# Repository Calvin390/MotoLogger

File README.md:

# Motologger

**Motologger** is a modular motorcycle data logger built around an ESP32-S3.  
The goal of the project is to record useful riding and vehicle dynamics data from a motorcycle that does not have a factory ECU or CAN bus.
The system is designed to collect data from external sensor modules over CAN and log it to a microSD card for later analysis.

> Current target platform: 2001 Suzuki SV650  
> Current firmware target: ESP32-S3 using ESP-IDF in C with FreeRTOS task/queue architecture

---

## Project Goals

Motologger is intended to be a compact, low-cost motorcycle telemetry system capable of logging:
- IMU data such as acceleration, gyro, and estimated lean angle
- GPS position and speed
- CAN messages from external daughterboards
- Timestamped CSV data to a microSD card
- Future expansion for additional sensors such as throttle position, brake pressure, wheel speed, and steering angle

The long-term goal is to build a modular logging and display system that can support both post-ride analysis and a future visor-mounted HUD.

---

## Current Status

**Status: PCB Bring-up and Firmware Flashing 

The prototype board has been assembled and is ready to be flashed using backup UART via ESP32 pins instead of USB-C due to anchoring issues with the receptacle. The ESP32 has been confirmed alive by both oscilloscope readings and reading TX data through TeraTerm coming from the ESP32.

Current focus:
Flashing firmware via UART to the ESP32 and confirming proper idle CAN traffic through an oscilloscope.

Hardware is in its first prototype revision and may change in future spins based on bring-up results.
---

## System Overview

The Motologger system is split into a main controller board and external sensor modules.

```text
        +--------------------+
        |    GPS Module      |
        |   u-blox M10       |
        +----------+---------+
                   |
                   | CAN
                   |
 +-----------------v-----------------+
|          Motologger Mainboard      |
|                                    |
| ESP32-S3-WROOM                     |
|  Power Stage (fuse/TVS/Schottky,   |
|    12V→5V→3.3V regulation)         |
|  microSD Card                      |
|  CAN Transceiver                   |
|  USB-C Debug/Programming           |
|  12V Motorcycle Power Input        |
 +-----------------^-----------------+
                   |
                   | CAN
                   |
        +----------+---------+
        |     IMU Module     |
        |   ICM-20948        |
        +--------------------+

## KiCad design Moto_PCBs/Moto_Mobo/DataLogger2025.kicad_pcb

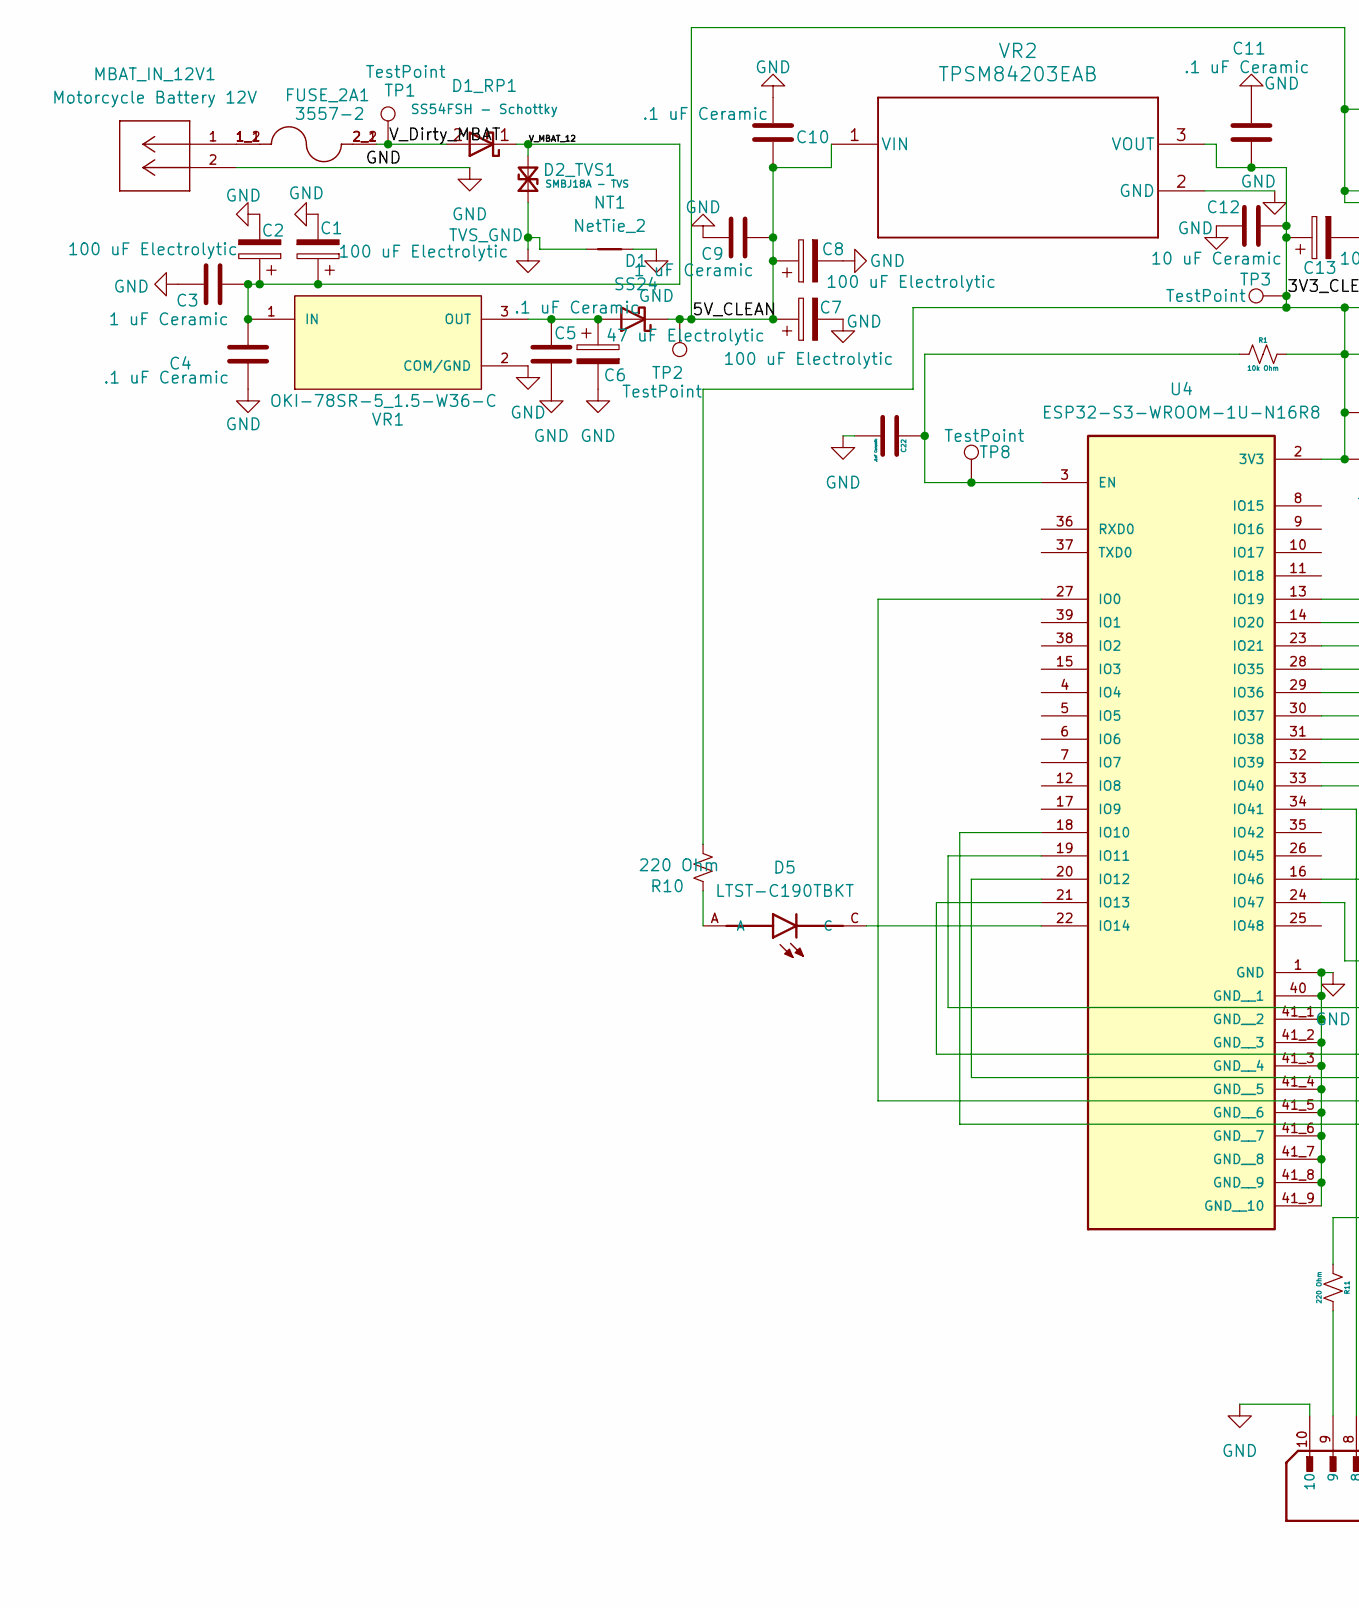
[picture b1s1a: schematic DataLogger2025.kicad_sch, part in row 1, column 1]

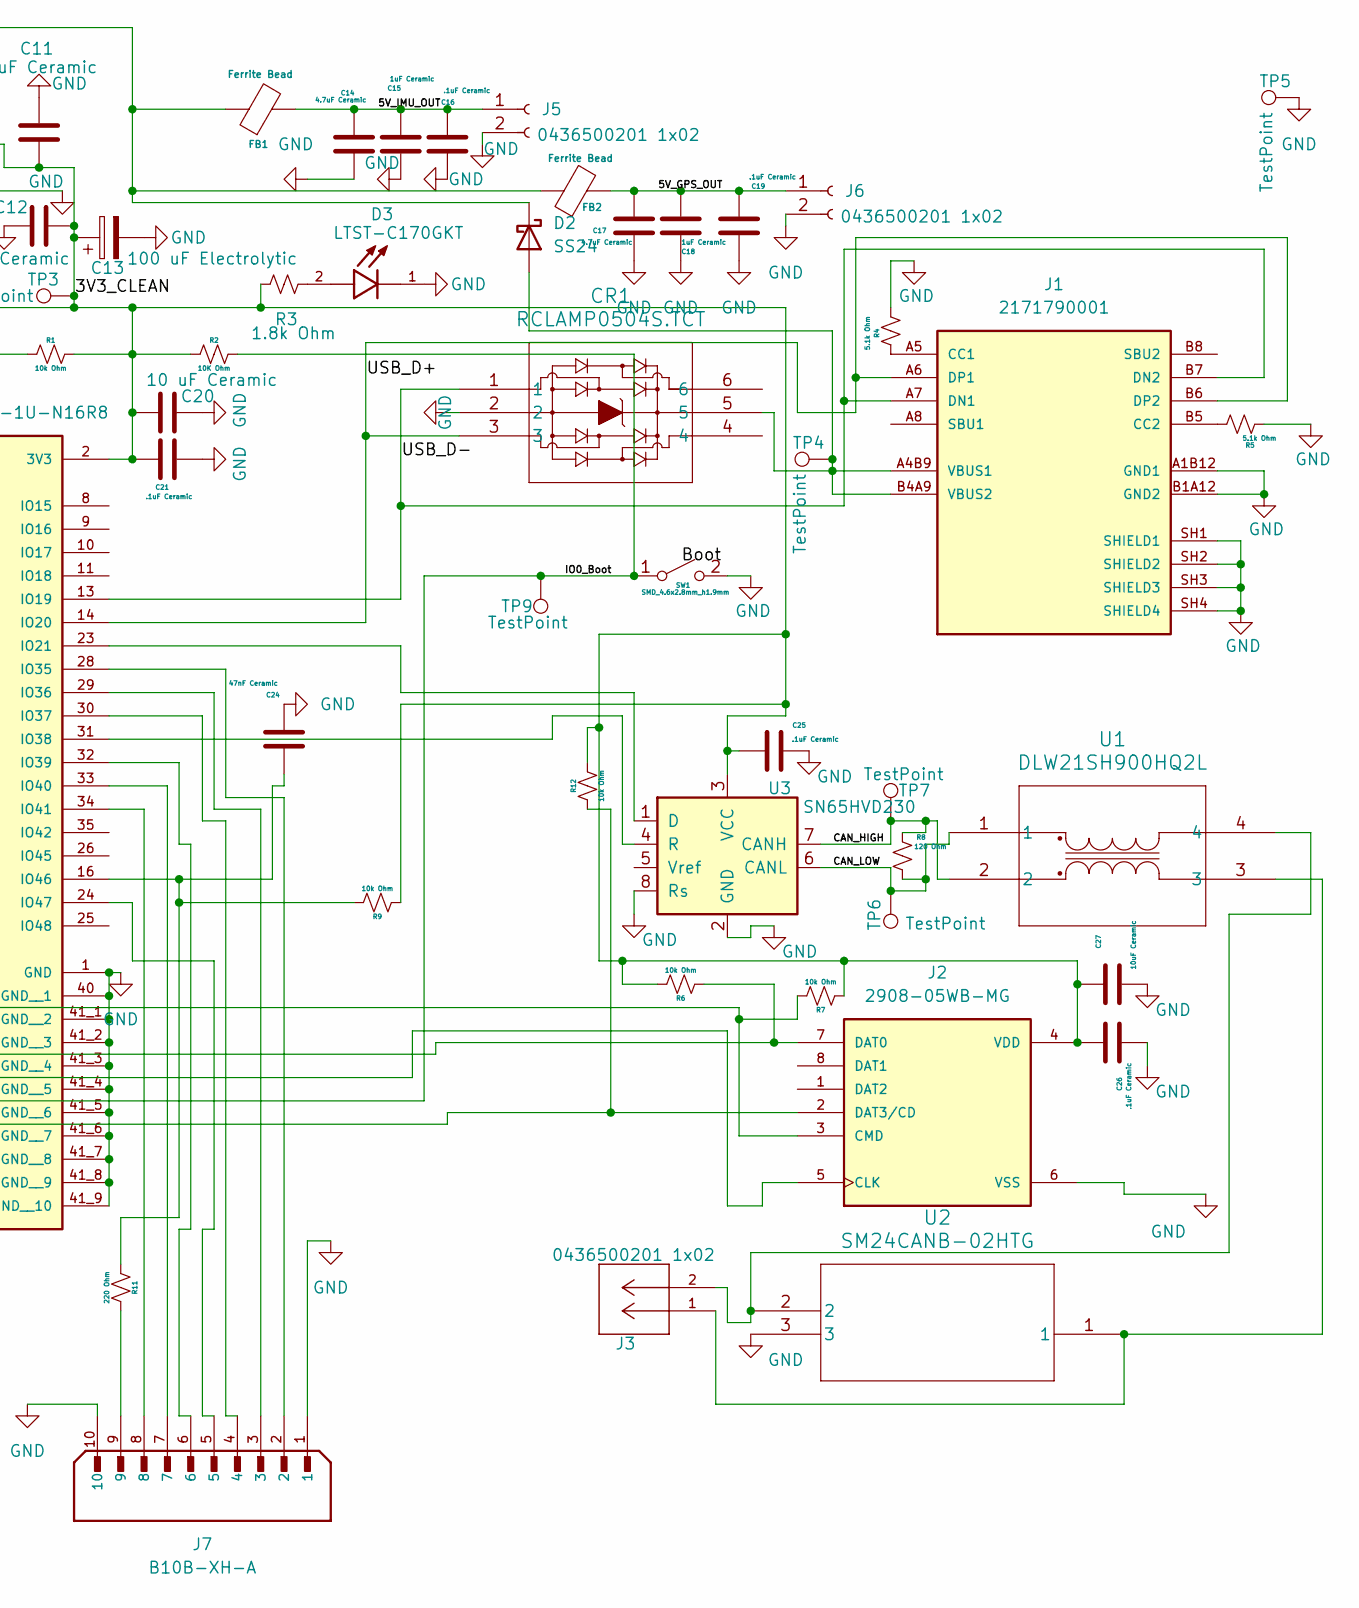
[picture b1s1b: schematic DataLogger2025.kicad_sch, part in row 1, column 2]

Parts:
C1, C2, C7, C8, C13: 100 uF Electrolytic; CP_Radial_D8.0mm_P2.50mm
C3, C9: 1 uF Ceramic; C_1206_3216Metric_Pad1.33x1.80mm_HandSolder
C4, C5, C10, C11: .1 uF Ceramic; C_1206_3216Metric_Pad1.33x1.80mm_HandSolder
C6: 47 uF Electrolytic; CP_Radial_D6.3mm_P2.50mm
C12, C20: 10 uF Ceramic; C_1206_3216Metric_Pad1.33x1.80mm_HandSolder
C14, C17: 4.7uF Ceramic; C_1206_3216Metric_Pad1.33x1.80mm_HandSolder
C15, C18: 1uF Ceramic; C_1206_3216Metric_Pad1.33x1.80mm_HandSolder
C16, C19, C21, C22, C25, C26: .1uF Ceramic; C_1206_3216Metric_Pad1.33x1.80mm_HandSolder
C24: 47nF Ceramic; C_1206_3216Metric_Pad1.33x1.80mm_HandSolder
C27: 10uF Ceramic; C_1206_3216Metric_Pad1.33x1.80mm_HandSolder
CR1: RCLAMP0504S.TCT; SC70-6L_RCLAMP_1p75x3p1-0p95_SEM
D1, D2: SS24; SOD-123F_ONS
D1_RP1: SS54FSH - Schottky; D_SMB
D2_TVS1: SMBJ18A - TVS; D_SMB_Handsoldering
D3: LTST-C170GKT; LED_LTST-C170GKT; PARTREV I; DigiKey_Part_Number 160-1179-1-ND
D5: LTST-C190TBKT; LEDM1608X80; DigiKey_Part_Number 160-1646-1-ND
FB1, FB2: Ferrite Bead; L_1206_3216Metric_Pad1.42x1.75mm_HandSolder
FUSE_2A1: 3557-2; FUSE_3557-2; PARTREV D; DigiKey_Part_Number 36-3557-2-ND
J1: 2171790001; MOLEX_2171790001; PARTREV A1; DigiKey_Part_Number 900-2171790001CT-ND
J2: 2908-05WB-MG; 3M_2908-05WB-MG; DigiKey_Part_Number 3M5607CT-ND
J3: 0436500201 1x02; CONN_SD-43650-001_02_MOL; MANUFACTURER_PART_NUMBER 436500201
J5, J6: 0436500201 1x02; Molex_Micro-Fit_3.0_43650-0200_1x02_P3.00mm_Horizontal
J7: B10B-XH-A; JST_B10B-XH-A; PARTREV 7/4/21; DigiKey_Part_Number 455-B10B-XH-A-ND
MBAT_IN_12V1: Motorcycle Battery 12V; CONN_SD-43650-001_02_MOL; MANUFACTURER_PART_NUMBER 436500201
NT1: NetTie_2; NetTie-2_SMD_Pad0.5mm
R1, R6, R7, R9, R12: 10k Ohm; R_1206_3216Metric_Pad1.30x1.75mm_HandSolder
R2: 10K Ohm; R_1206_3216Metric_Pad1.30x1.75mm_HandSolder
R3: 1.8k Ohm; R_1206_3216Metric_Pad1.30x1.75mm_HandSolder
R4, R5: 5.1k Ohm; R_1206_3216Metric_Pad1.30x1.75mm_HandSolder
R8: 120 Ohm; R_Axial_DIN0204_L3.6mm_D1.6mm_P5.08mm_Horizontal
R10, R11: 220 Ohm; R_1206_3216Metric_Pad1.30x1.75mm_HandSolder
SW1: SMD_4.6x2.8mm_h1.9mm; Push_SMD_4.6x2.8mm_h1.9mm
TP1, TP2, TP3, TP4, TP5, TP6, TP7, TP9: TestPoint; TestPoint_Pad_1.5x1.5mm
TP8: TestPoint; TestPoint_Pad_1.0x1.0mm
U1: DLW21SH900HQ2L; DLW21SH_MUR
U2: SM24CANB-02HTG; SOT23-3_SM24CANB-02HTG_LTF
U3: SN65HVD230; SOIC-8_3.9x4.9mm_P1.27mm
U4: ESP32-S3-WROOM-1U-N16R8; XCVR_ESP32-S3-WROOM-1U-N16R8; PARTREV v1.1; DigiKey_Part_Number 1965-ESP32-S3-WROOM-1U-N16R8CT-ND
VR1: OKI-78SR-5_1.5-W36-C; CONV_OKI-78SR-5_1.5-W36-C; PARTREV N/A; DigiKey_Part_Number 811-2196-5-ND
VR2: TPSM84203EAB; EAB0003A

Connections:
/3V3_CLEAN: C11.2, C12.2, C13.1, C20.2, C21.1, C25.1, C26.1, C27.1, J2.4 (VDD), R1.1, R2.2, R3.1, R6.1, R7.2, R9.2, R10.1, R12.1, TP3.1 (1_1), U3.3 (VCC), U4.2 (3V3), VR2.3 (VOUT)
/5V_CLEAN: C7.1, C8.1, C9.2, C10.2, D1.1 (K), D2.1 (K), FB1.1, FB2.1, TP2.1 (1_1), VR2.1 (VIN)
/5V_GPS_OUT: C17.1, C18.1, C19.1, FB2.2, J6.1
/5V_IMU_OUT: C14.1, C15.1, C16.1, FB1.2, J5.1
/CAN_HIGH: R8.2, TP7.1 (1_1), U1.2, U3.7 (CANH)
/CAN_LOW: R8.1, TP6.1 (1_1), U1.1, U3.6 (CANL)
/IO0_Boot: R2.1, SW1.1 (A), TP9.1 (1_1), U4.27 (IO0)
/USB_D+: CR1.3, J1.A6 (DP1), J1.B6 (DP2), U4.14 (IO20)
/USB_D-: CR1.1, J1.A7 (DN1), J1.B7 (DN2), U4.13 (IO19)
/V_Dirty_MBAT: D1_RP1.2 (A), FUSE_2A1.2_1, FUSE_2A1.2_2, TP1.1 (1_1)
/V_MBAT_12: C1.1, C2.1, C3.2, C4.2, D1_RP1.1 (K), D2_TVS1.2 (A2), VR1.1 (IN)
GND: C1.2, C2.2, C3.1, C4.1, C5.1, C6.2, C7.2, C8.2, C9.1, C10.1, C11.1, C12.1, C13.2, C14.2, C15.2, C16.2, C17.2, C18.2, C19.2, C20.1, C21.2, C22.2, C24.1, C25.2, C26.2, C27.2, CR1.2, D3.1, J1.A1B12 (GND1), J1.B1A12 (GND2), J1.SH1 (SHIELD1), J1.SH2 (SHIELD2), J1.SH3 (SHIELD3), J1.SH4 (SHIELD4), J2.6 (VSS), J5.2, J6.2, J7.1, J7.10, MBAT_IN_12V1.2, NT1.2, R4.1, R5.1, SW1.2 (B), TP5.1 (1_1), U2.3, U3.2 (GND), U3.8 (Rs), U4.1 (GND), U4.40 (GND__1), U4.41_1 (GND__2), U4.41_2 (GND__3), U4.41_3 (GND__4), U4.41_4 (GND__5), U4.41_5 (GND__6), U4.41_6 (GND__7), U4.41_7 (GND__8), U4.41_8 (GND__9), U4.41_9 (GND__10), VR1.2 (COM/GND), VR2.2 (GND)
unnamed: C5.2, C6.1, D1.2 (A), VR1.3 (OUT)
unnamed: CR1.5, D2.2 (A), J1.A4B9 (VBUS1), J1.B4A9 (VBUS2), TP4.1 (1_1)
unnamed: D3.2, R3.2
unnamed: D5.A, R10.2
unnamed: FUSE_2A1.1_1, FUSE_2A1.1_2, MBAT_IN_12V1.1
unnamed: J1.A5 (CC1), R4.2
unnamed: J1.B5 (CC2), R5.2
unnamed: J2.5 (CLK), U4.20 (IO12)
unnamed: J2.3 (CMD), R7.1, U4.19 (IO11)
unnamed: J2.7 (DAT0), R6.2, U4.21 (IO13)
unnamed: J2.2 (DAT3/CD), R12.2, U4.18 (IO10)
unnamed: J3.1, U1.3, U2.1
unnamed: J3.2, U1.4, U2.2
unnamed: J7.9, R11.1
unnamed: U3.1 (D), U4.23 (IO21)
unnamed: U3.4 (R), U4.31 (IO38)
unnamed: C22.1, R1.2, TP8.1 (1_1), U4.3 (EN)
unnamed: D5.C, U4.22 (IO14)
unnamed: J7.2, U4.28 (IO35)
unnamed: J7.3, U4.29 (IO36)
unnamed: J7.4, U4.30 (IO37)
unnamed: J7.6, U4.32 (IO39)
unnamed: J7.7, U4.33 (IO40)
unnamed: J7.8, U4.34 (IO41)
unnamed: C24.2, R9.1, R11.2, U4.16 (IO46)
unnamed: J7.5, U4.24 (IO47)
TVS_GND: D2_TVS1.1 (A1), NT1.1

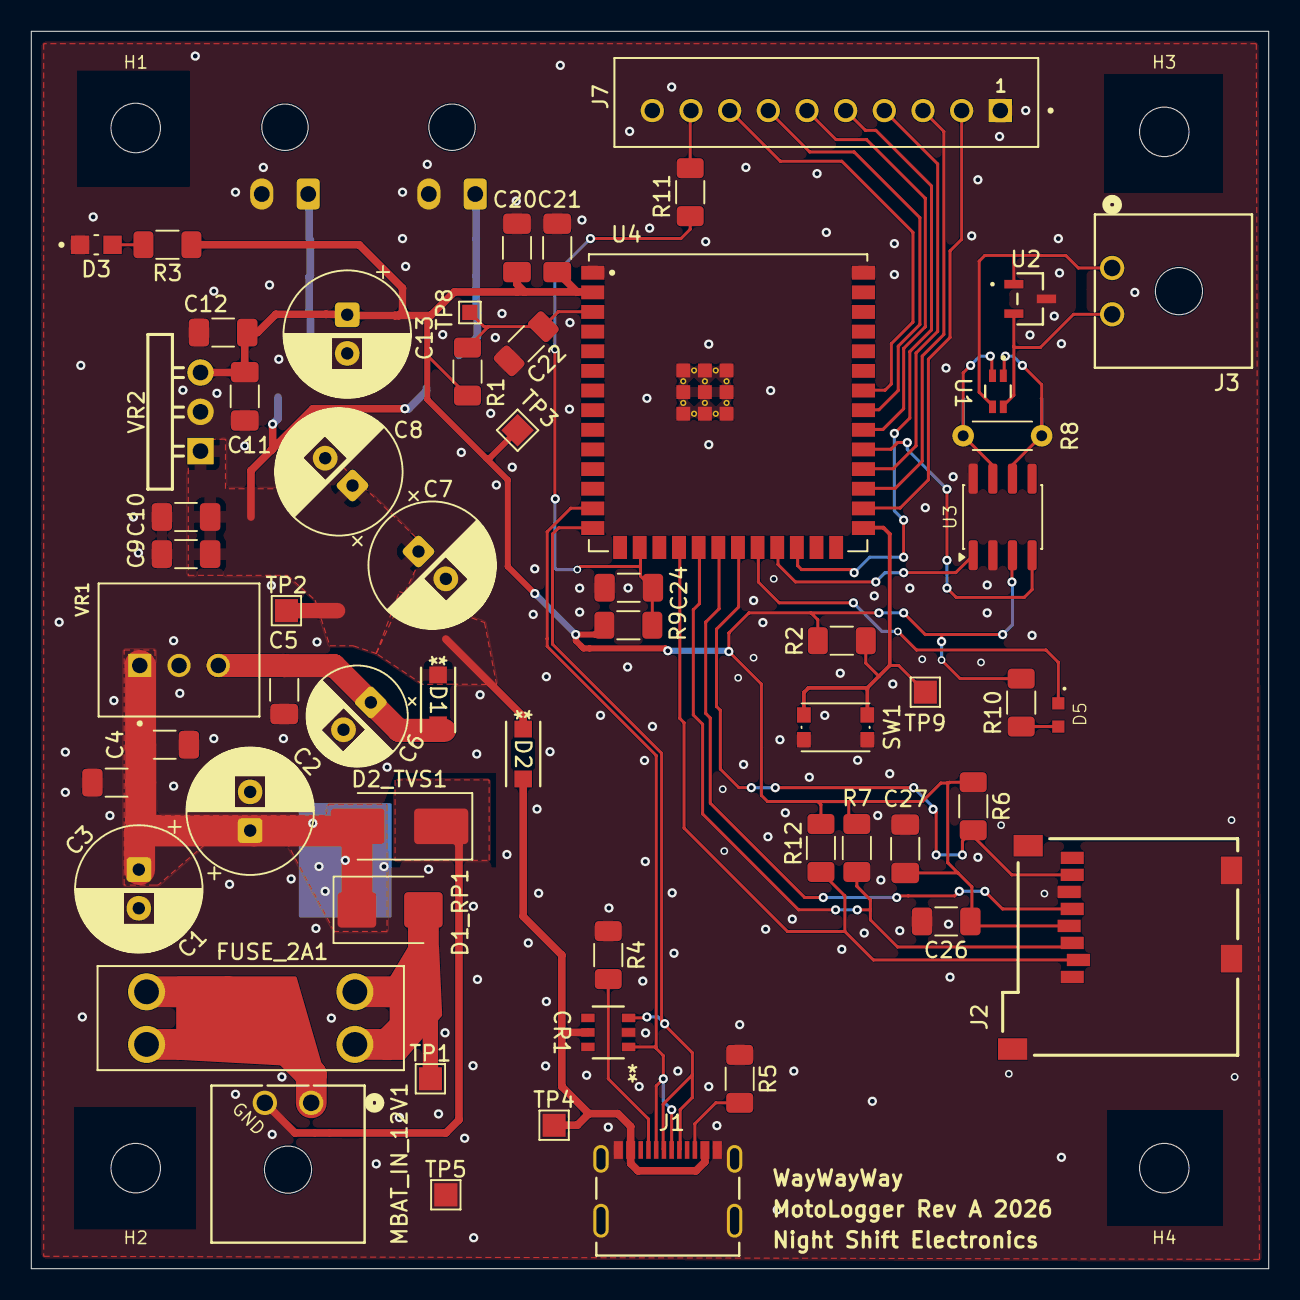
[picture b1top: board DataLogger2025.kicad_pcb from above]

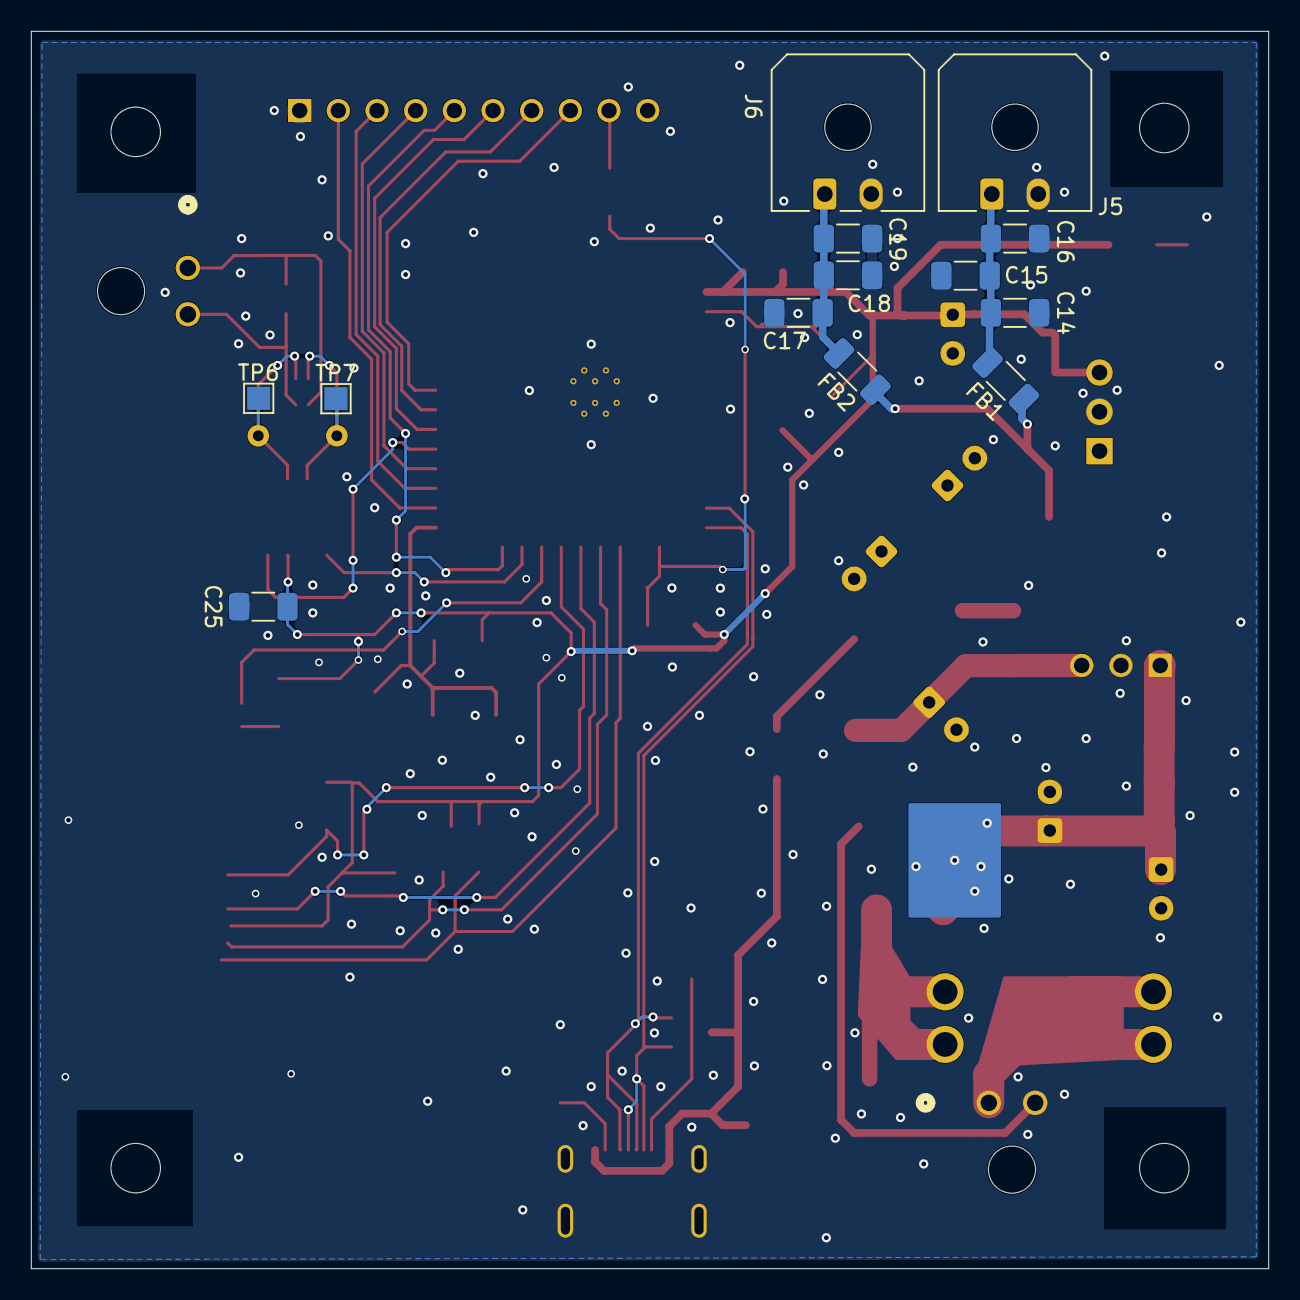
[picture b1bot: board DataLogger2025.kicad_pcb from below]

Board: 2 copper layers, 80.0 x 80.0 mm, 76 parts (13 on the bottom side), 39 nets.

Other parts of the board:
H1, H2, H3, H4: MountingHole; MountingHole_3.2mm_M3

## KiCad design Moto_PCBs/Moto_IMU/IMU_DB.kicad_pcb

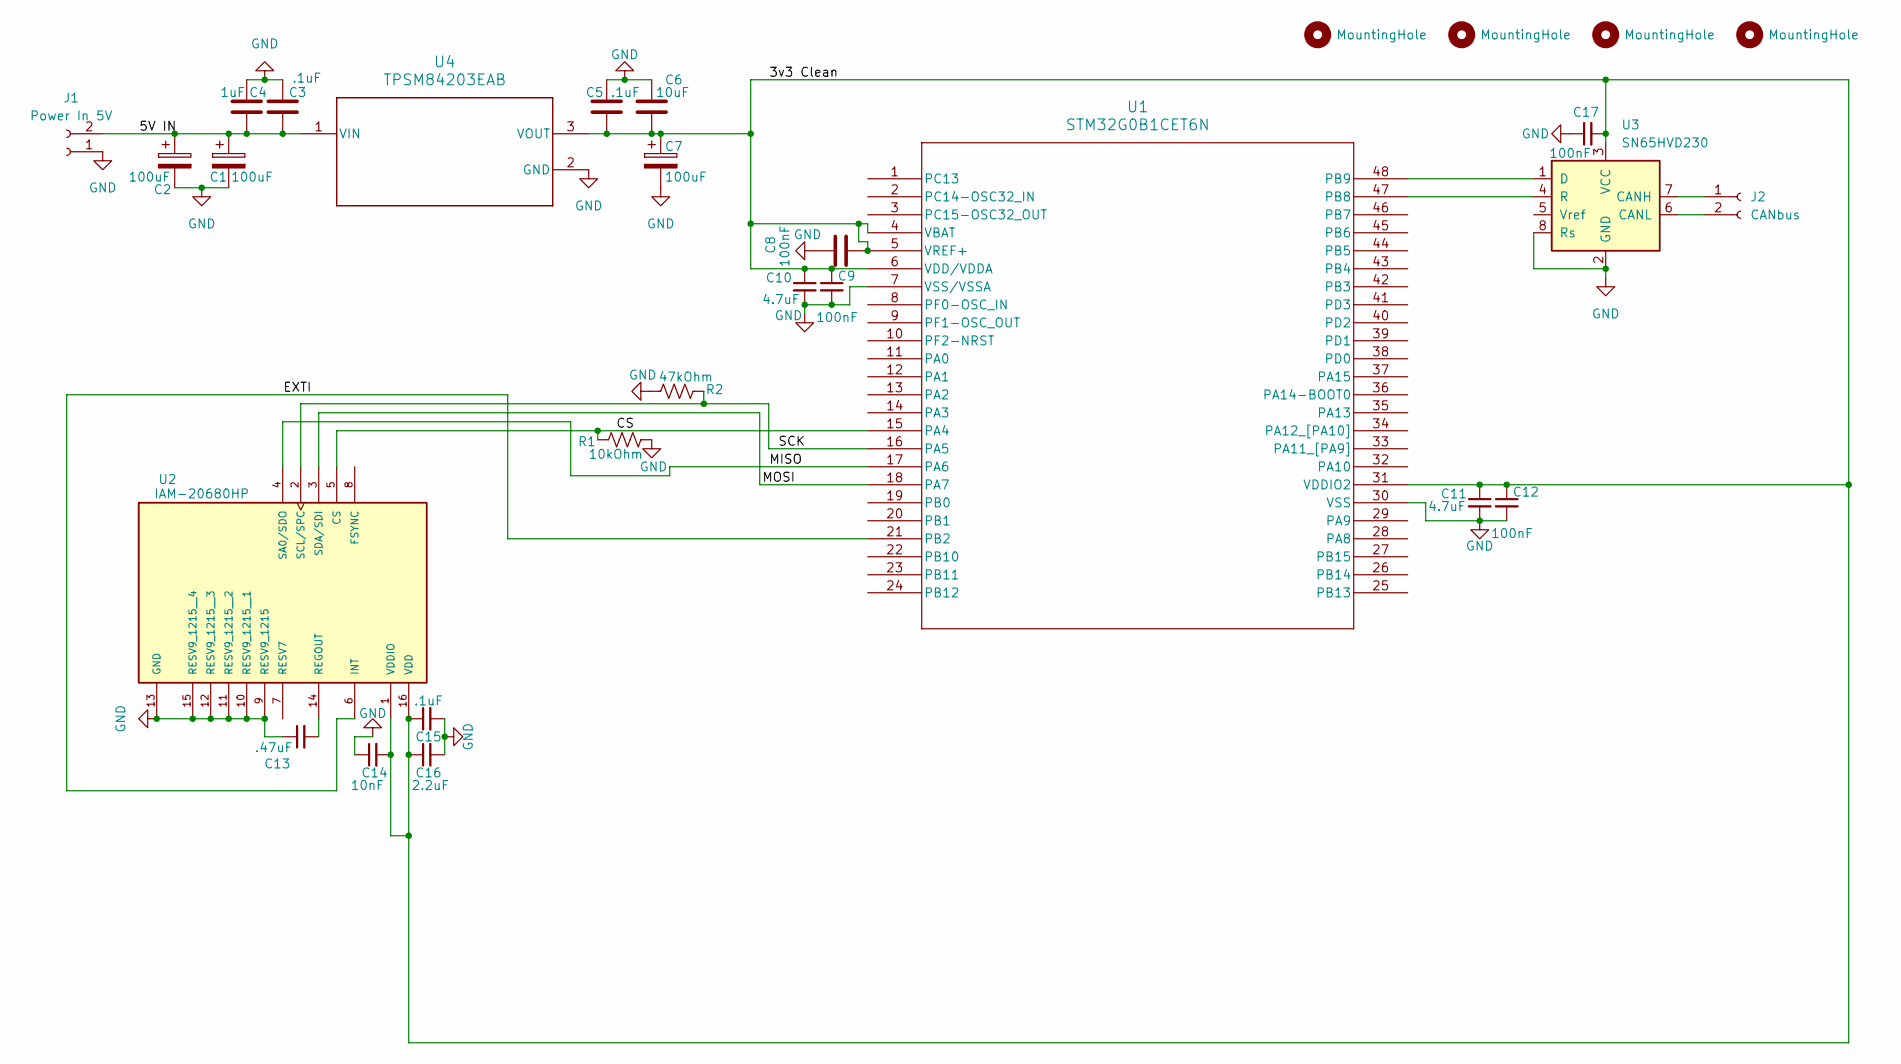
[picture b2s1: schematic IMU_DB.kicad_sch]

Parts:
C1, C2, C7: 100uF; CP_Radial_D5.0mm_P2.50mm
C3, C5, C15: .1uF; C_0805_2012Metric_Pad1.18x1.45mm_HandSolder
C4: 1uF; C_0805_2012Metric_Pad1.18x1.45mm_HandSolder
C6: 10uF; C_0805_2012Metric_Pad1.18x1.45mm_HandSolder
C8, C9, C12, C17: 100nF; C_0805_2012Metric_Pad1.18x1.45mm_HandSolder
C10, C11: 4.7uF; C_0805_2012Metric_Pad1.18x1.45mm_HandSolder
C13: .47uF; C_0805_2012Metric_Pad1.18x1.45mm_HandSolder
C14: 10nF; C_0805_2012Metric_Pad1.18x1.45mm_HandSolder
C16: 2.2uF; C_0805_2012Metric_Pad1.18x1.45mm_HandSolder
H1, H2, H3, H4: MountingHole; MountingHole_2.2mm_M2
J1: Power In 5V; CONN_SD-43650-001_02_MOL
J2: CANbus; CONN_SD-43650-001_02_MOL
R1: 10kOhm; R_0805_2012Metric_Pad1.20x1.40mm_HandSolder
R2: 47kOhm; R_0805_2012Metric_Pad1.20x1.40mm_HandSolder
U1: STM32G0B1CET6N; LQFP48_STM
U2: IAM-20680HP; PQFN50P300X300X80-16N
U3: SN65HVD230; SOIC-8_3.9x4.9mm_P1.27mm
U4: TPSM84203EAB; EAB0003A

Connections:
/3v3 Clean: C5.2, C6.2, C7.1, C8.2, C9.1, C10.1, C11.1, C12.1, C14.2, C15.1, C16.1, C17.2, U1.4 (VBAT), U1.5 (VREF+), U1.6 (VDD/VDDA), U1.31 (VDDIO2), U2.1 (VDDIO), U2.16 (VDD), U3.3 (VCC), U4.3 (VOUT)
/5V IN: C1.1, C2.1, C3.2, C4.2, J1.2, U4.1 (VIN)
/CS: R1.1, U1.15 (PA4), U2.5 (CS)
/EXTI: U1.21 (PB2), U2.6 (INT)
/MISO: U1.17 (PA6), U2.4 (SA0/SDO)
/MOSI: U1.18 (PA7), U2.3 (SDA/SDI)
/SCK: R2.1, U1.16 (PA5), U2.2 (SCL/SPC)
GND: C1.2, C2.2, C3.1, C4.1, C5.1, C6.1, C7.2, C8.1, C9.2, C10.2, C11.2, C12.2, C13.1, C14.1, C15.2, C16.2, C17.1, J1.1, R1.2, R2.2, U1.7 (VSS/VSSA), U1.30 (VSS), U2.9 (RESV9_1215), U2.10 (RESV9_1215__1), U2.11 (RESV9_1215__2), U2.12 (RESV9_1215__3), U2.13 (GND), U2.15 (RESV9_1215__4), U3.2 (GND), U3.8 (Rs), U4.2 (GND)
unnamed: J2.1, U3.7 (CANH)
unnamed: J2.2, U3.6 (CANL)
unnamed: U1.47 (PB8), U3.4 (R)
unnamed: U1.48 (PB9), U3.1 (D)
unnamed: C13.2, U2.14 (REGOUT)

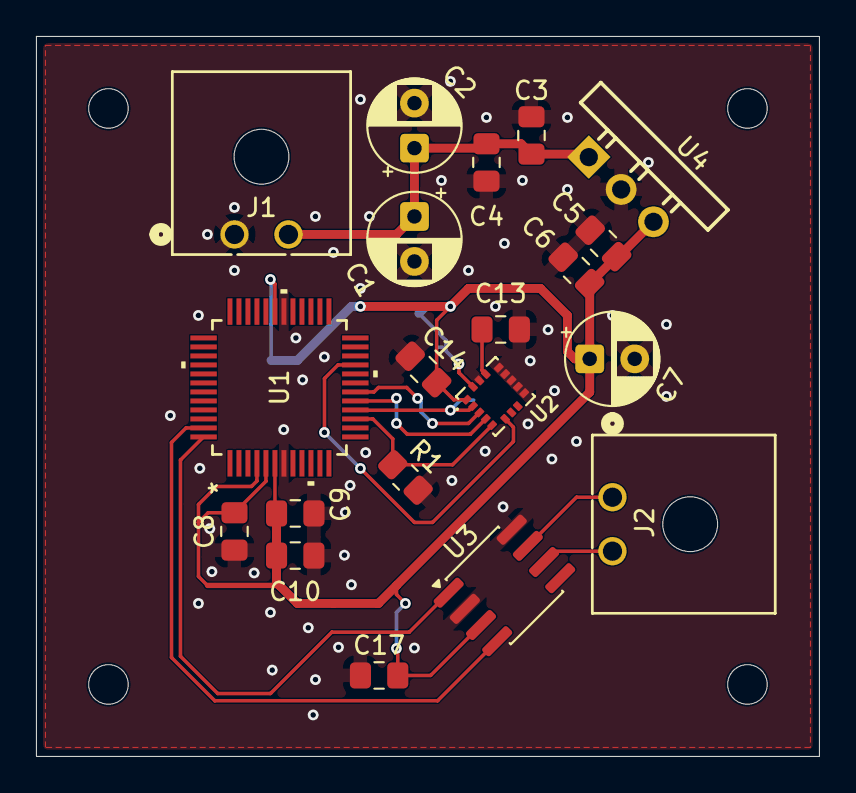
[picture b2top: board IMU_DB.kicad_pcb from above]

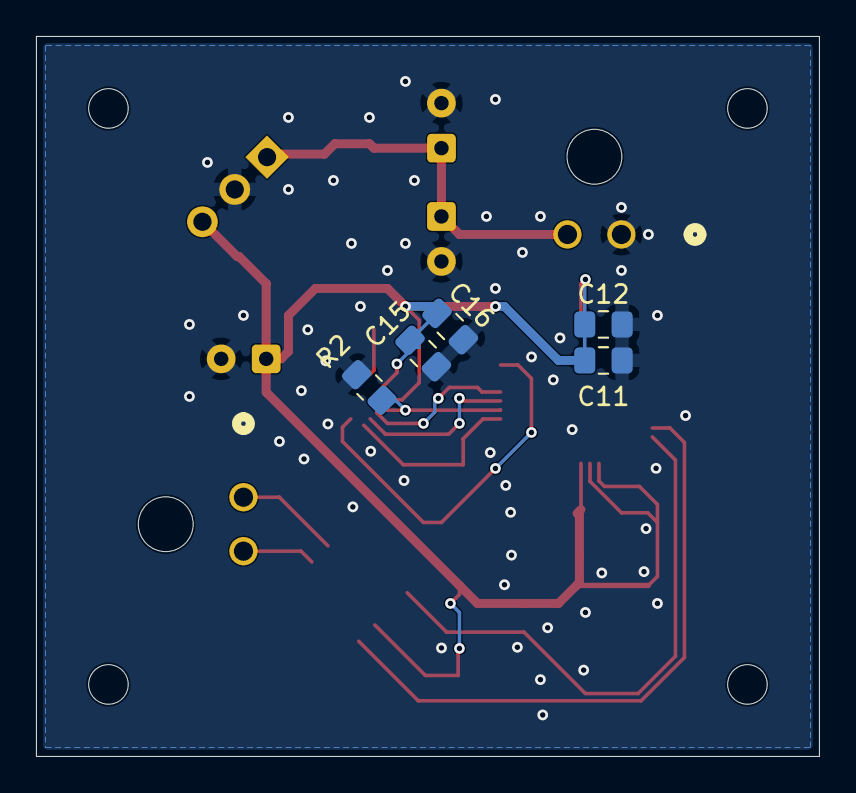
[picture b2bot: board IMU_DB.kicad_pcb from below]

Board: 2 copper layers, 43.5 x 40.0 mm, 29 parts (5 on the bottom side), 13 nets.

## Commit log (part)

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2026-06-29 Folder Tree Readjustment
2026-06-29 PCB File readjustment
2026-06-29 Update CMakeLists.txt to include required components
2026-06-30 Final Mobo GBR/PCB Files before PCBWAY Order
2026-06-30 Add can_protocol.c to CMakeLists.txt
